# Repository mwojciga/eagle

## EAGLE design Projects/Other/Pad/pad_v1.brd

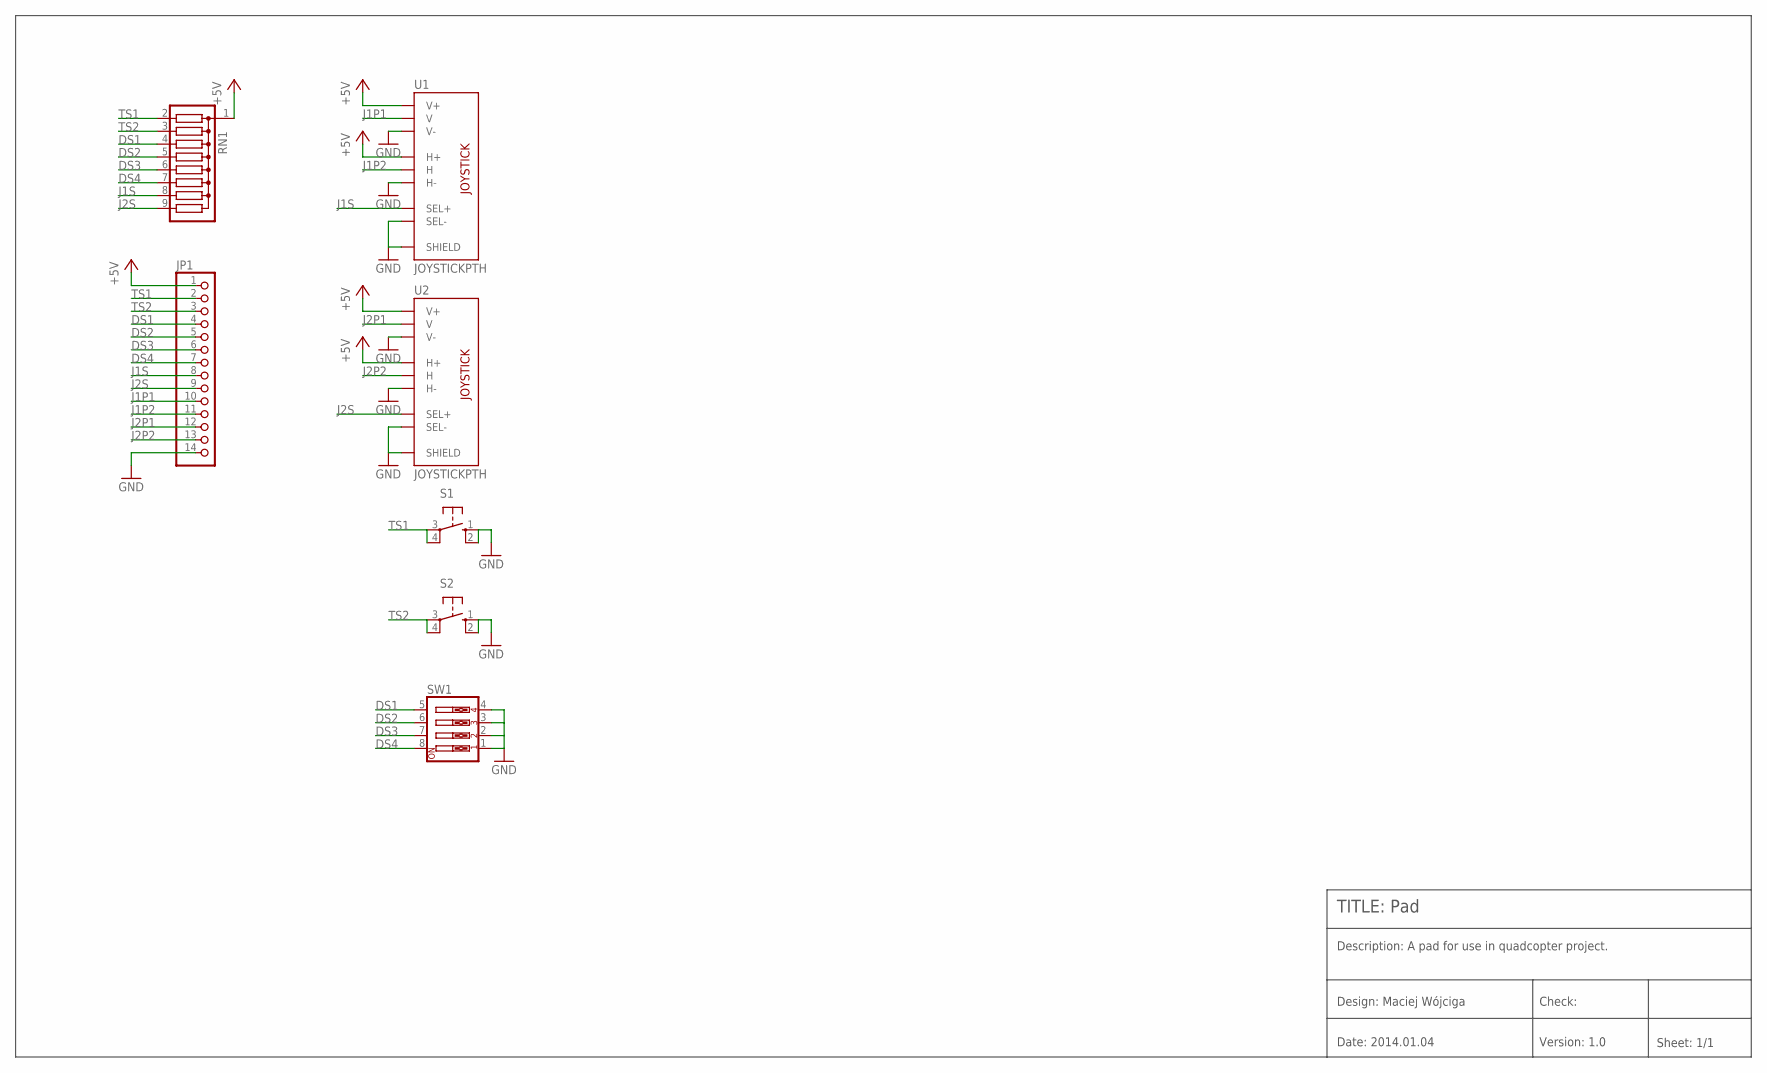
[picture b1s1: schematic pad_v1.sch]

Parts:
JP1: PINHD-1X14; 1X14
RN1: G08R; SIL9
S1, S2: 10-XX; B3F-10XX
SW1: SW_DIP-4; EDG-04
U1, U2: JOYSTICKPTH; JOYSTICK

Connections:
+5V: JP1.1, RN1.1, U1.H1 (H+), U1.V1 (V+), U2.H1 (H+), U2.V1 (V+)
DS1: JP1.4, RN1.4, SW1.5
DS2: JP1.5, RN1.5, SW1.6
DS3: JP1.6, RN1.6, SW1.7
DS4: JP1.7, RN1.7, SW1.8
GND: JP1.14, S1.1 (S), S1.2 (S1), S2.1 (S), S2.2 (S1), SW1.1, SW1.2, SW1.3, SW1.4, U1.B2A (SEL-), U1.B2B (SEL-), U1.H3 (H-), U1.MOUNT1 (SHIELD), U1.MOUNT2 (SHIELD), U1.MOUNT3 (SHIELD), U1.MOUNT4 (SHIELD), U1.V3 (V-), U2.B2A (SEL-), U2.B2B (SEL-), U2.H3 (H-), U2.MOUNT1 (SHIELD), U2.MOUNT2 (SHIELD), U2.MOUNT3 (SHIELD), U2.MOUNT4 (SHIELD), U2.V3 (V-)
J1P1: JP1.10, U1.V2 (V)
J1P2: JP1.11, U1.H2 (H)
J1S: JP1.8, RN1.8, U1.B1A (SEL+), U1.B1B (SEL+)
J2P1: JP1.12, U2.V2 (V)
J2P2: JP1.13, U2.H2 (H)
J2S: JP1.9, RN1.9, U2.B1A (SEL+), U2.B1B (SEL+)
TS1: JP1.2, RN1.2, S1.3, S1.4 (P1)
TS2: JP1.3, RN1.3, S2.3, S2.4 (P1)

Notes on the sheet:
TITLE: Pad
Design: Maciej Wójciga
Check:
Date: 2014.01.04
Version: 1.0
Sheet: 1/1
Description: A pad for use in quadcopter project.

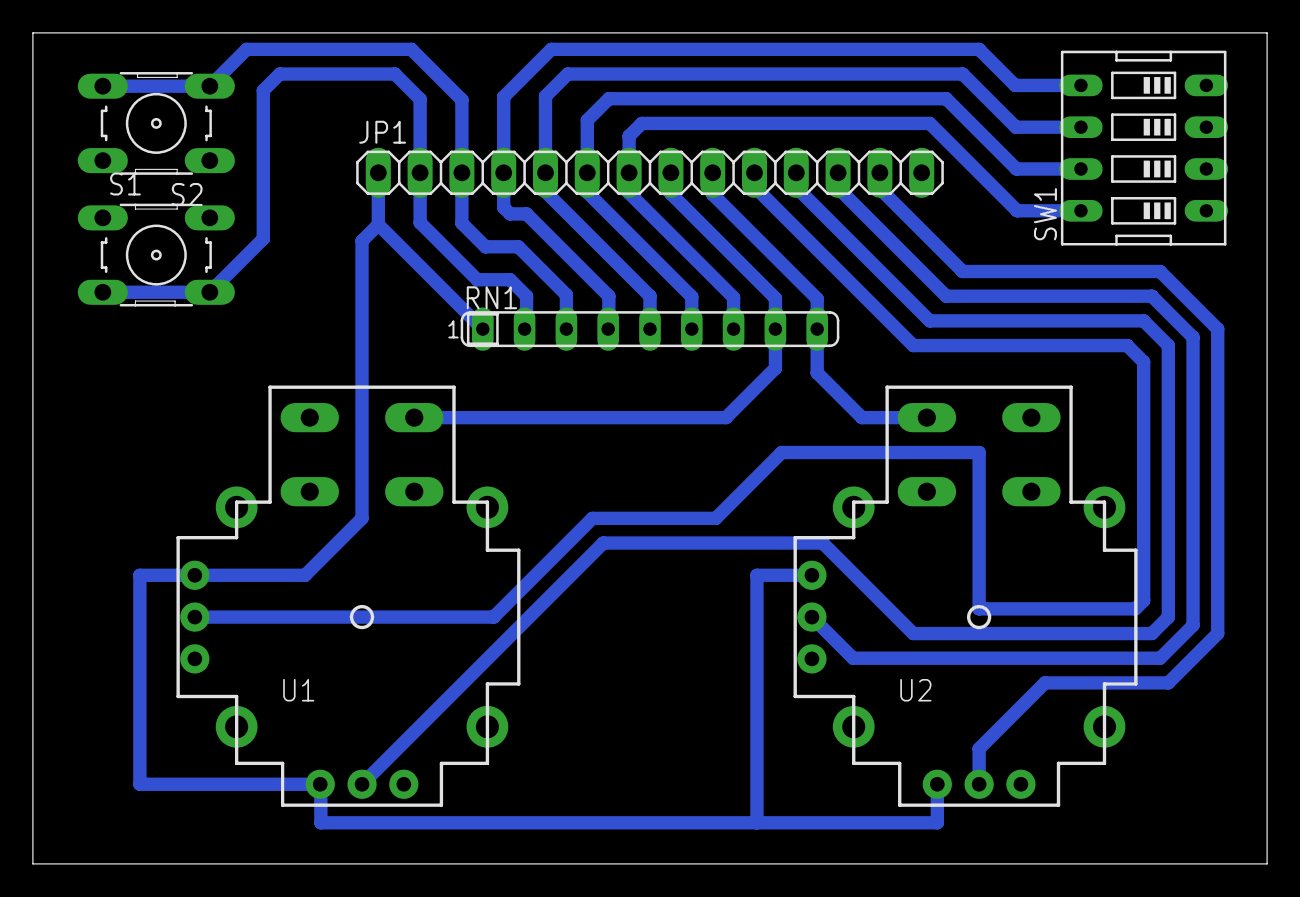
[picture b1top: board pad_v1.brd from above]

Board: 2 copper layers, 75.0 x 50.5 mm, 7 parts (0 on the bottom side), 14 nets.

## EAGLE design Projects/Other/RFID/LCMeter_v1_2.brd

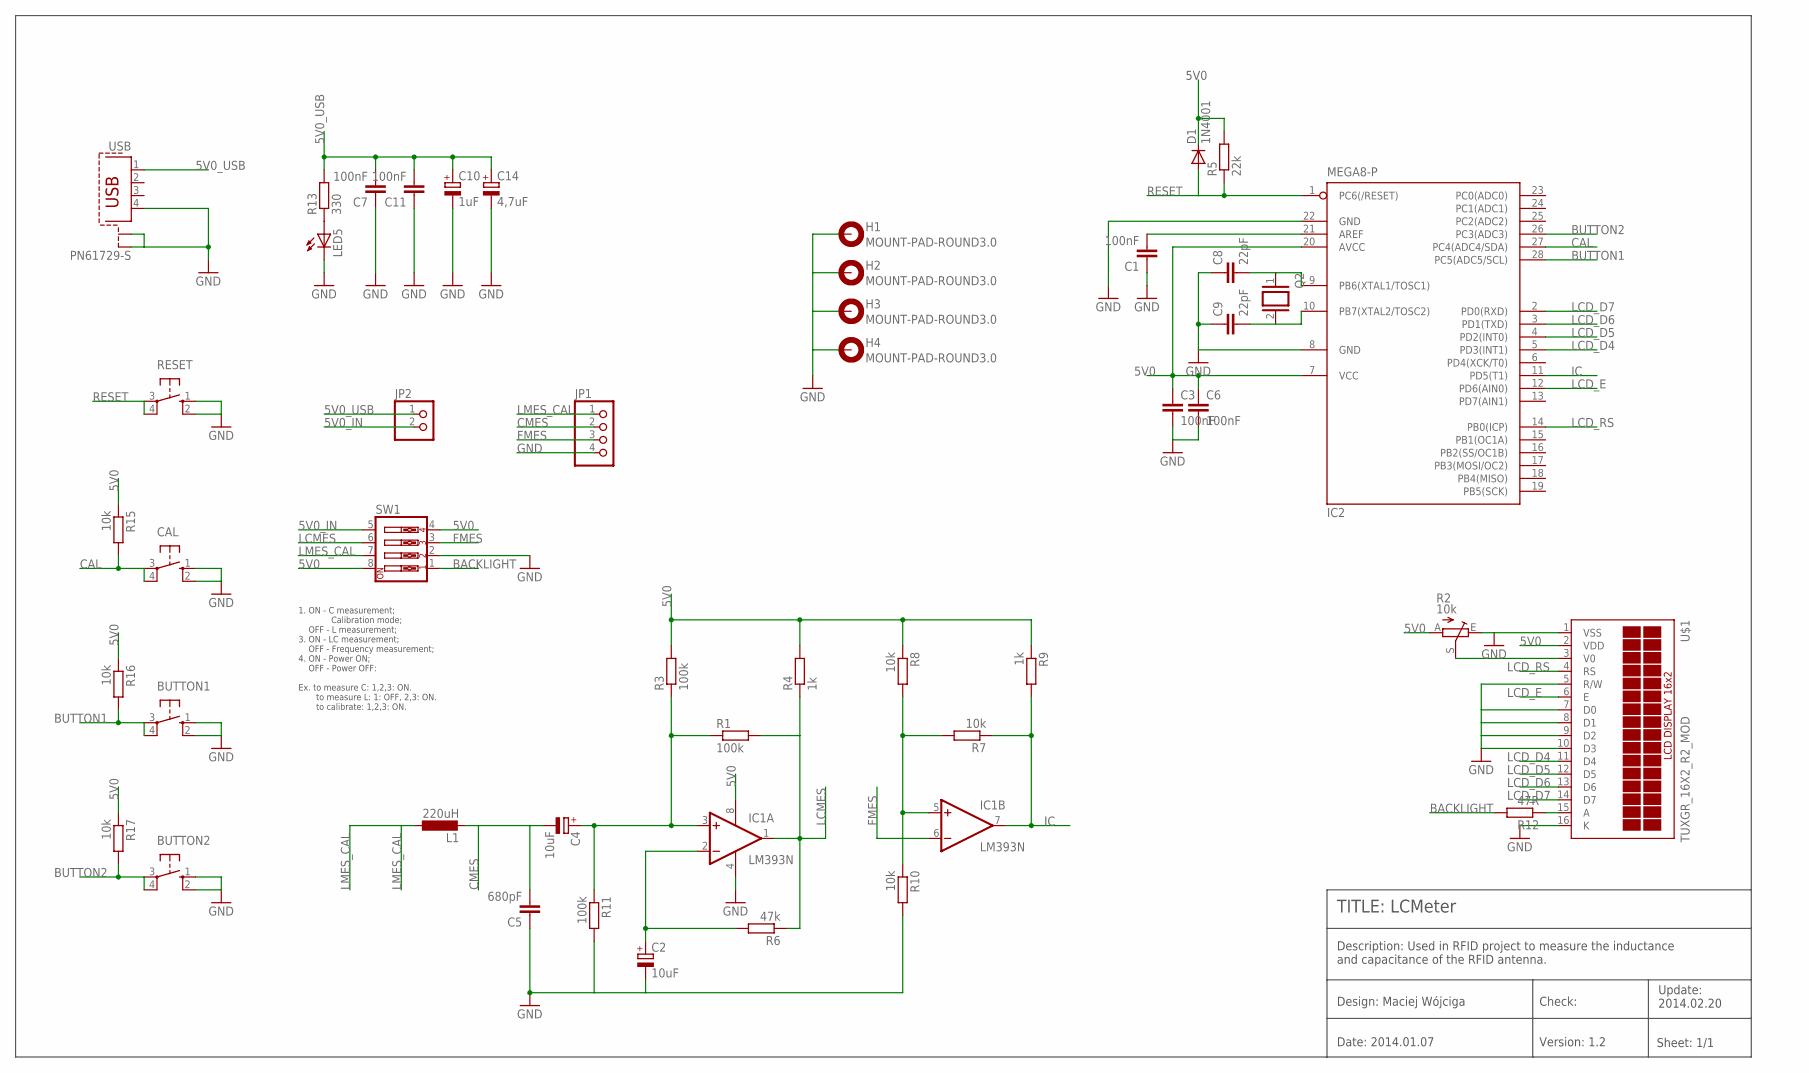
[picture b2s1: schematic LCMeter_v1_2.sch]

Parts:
BUTTON1, BUTTON2: 10-XX; B3F-10XX
C1, C3, C6, C7, C11: 100nF; C025-025X050
C2, C4: 10uF; E2,5-6E
C5: 680pF; C025-025X050
C8, C9: 22pF; C025-025X050
C10: 1uF; E2,5-5
C14: 4,7uF; E2,5-5
CAL: 10-XX; B3F-10XX
D1: 1N4001; DO41-10
H1, H2, H3, H4: MOUNT-PAD-ROUND3.0; 3,0-PAD
IC1: LM393N; DIL08
IC2: MEGA8-P; DIL28-3
JP1: PINHD-1X4; 1X04
JP2: PINHD-1X2/90; 1X02/90
L1: 220uH; 6000-XXXX-RC
LED5: LED3MM
Q2: XTAL/S; QS
R1, R3, R11: 100k; 0207/10
R2: 10k; RJ9W
R4, R9: 1k; 0207/10
R5: 22k; 0207/10
R6: 47k; 0207/10
R7, R8, R10, R15, R16, R17: 10k; 0207/10
R12: 47R; 0207/10
R13: 330; 0207/10
RESET: 10-XX; B3F-10XX
SW1: SW_DIP-4; EDG-04
U$1: TUXGR_16X2_R2_MOD
USB: PN61729-S

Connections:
5V0: C3.1, C6.1, D1.C, IC1.8 (V+), IC2.7 (VCC), IC2.20 (AVCC), R2.A, R3.2, R4.2, R5.2, R8.1, R9.1, R15.1, R16.1, R17.1, SW1.4, SW1.8, U$1.2 (VDD)
5V0_IN: JP2.2, SW1.5
5V0_USB: C7.2, C10.+, C11.2, C14.+, JP2.1, R13.2, USB.1
BACKLIGHT: R12.2, SW1.1
BUTTON1: BUTTON1.3, BUTTON1.4 (P1), IC2.28 (PC5(ADC5/SCL)), R16.2
BUTTON2: BUTTON2.3, BUTTON2.4 (P1), IC2.26 (PC3(ADC3)), R17.2
CAL: CAL.3, CAL.4 (P1), IC2.27 (PC4(ADC4/SDA)), R15.2
CMES: C4.-, C5.2, JP1.2, L1.2
FMES: IC1.6 (-IN), JP1.3, SW1.3
GND: BUTTON1.1 (S), BUTTON1.2 (S1), BUTTON2.1 (S), BUTTON2.2 (S1), C1.1, C2.-, C3.2, C5.1, C6.2, C7.1, C8.1, C9.1, C10.-, C11.1, C14.-, CAL.1 (S), CAL.2 (S1), H1.B3,0, H2.B3,0, H3.B3,0, H4.B3,0, IC1.4 (V-), IC2.8 (GND), IC2.22 (GND), JP1.4, LED5.K (C), R2.E, R10.2, R11.2, RESET.1 (S), RESET.2 (S1), SW1.2, U$1.1 (VSS), U$1.5 (R/W), U$1.7 (D0), U$1.8 (D1), U$1.9 (D2), U$1.10 (D3), U$1.16 (K), USB.4, USB.S1, USB.S2
IC: IC1.7 (OUT), IC2.11 (PD5(T1)), R7.1, R9.2
LCD_D4: IC2.5 (PD3(INT1)), U$1.11 (D4)
LCD_D5: IC2.4 (PD2(INT0)), U$1.12 (D5)
LCD_D6: IC2.3 (PD1(TXD)), U$1.13 (D6)
LCD_D7: IC2.2 (PD0(RXD)), U$1.14 (D7)
LCD_E: IC2.12 (PD6(AIN0)), U$1.6 (E)
LCD_RS: IC2.14 (PB0(ICP)), U$1.4 (RS)
LCMES: IC1.1 (OUT), R1.2, R4.1, R6.1, SW1.6
LMES_CAL: JP1.1, L1.1, SW1.7
unnamed: C1.2, IC2.21 (AREF)
unnamed: C2.+, IC1.2 (-IN), R6.2
unnamed: R2.S, U$1.3 (V0)
unnamed: C4.+, IC1.3 (+IN), R1.1, R3.1, R11.1
unnamed: LED5.A, R13.1
unnamed: IC1.5 (+IN), R7.2, R8.2, R10.1
unnamed: R12.1, U$1.15 (A)
unnamed: C8.2, IC2.9 (PB6(XTAL1/TOSC1)), Q2.1
unnamed: C9.2, IC2.10 (PB7(XTAL2/TOSC2)), Q2.2
RESET: D1.A, IC2.1 (PC6(/RESET)), R5.1, RESET.3, RESET.4 (P1)

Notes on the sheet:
TITLE: LCMeter
Design: Maciej Wójciga
Check:
Date: 2014.01.07
Version: 1.2
Sheet: 1/1
Description: Used in RFID project to measure the inductance and capacitance of the RFID antenna.
1. ON - C measurement; Calibration mode; OFF - L measurement; 3. ON - LC measurement; OFF - Frequency measurement; 4. ON - Power ON; OFF - Power OFF: Ex. to measure C: 1,2,3: ON. to measure L: 1: OFF, 2,3: ON. to calibrate: 1,2,3: ON.
Update: 2014.02.20

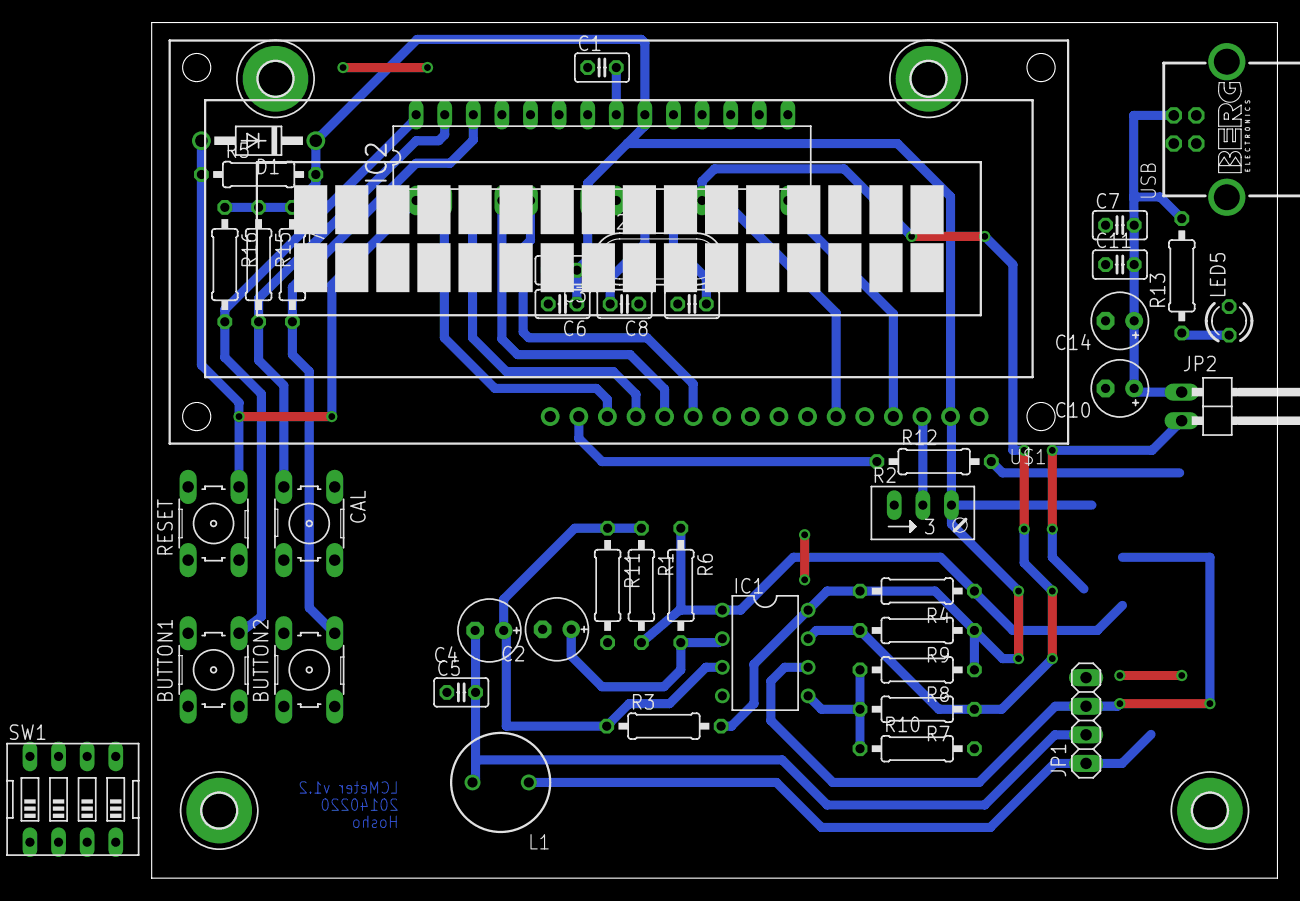
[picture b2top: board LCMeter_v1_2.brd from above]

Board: 2 copper layers, 100.0 x 76.0 mm, 47 parts (0 on the bottom side), 29 nets.

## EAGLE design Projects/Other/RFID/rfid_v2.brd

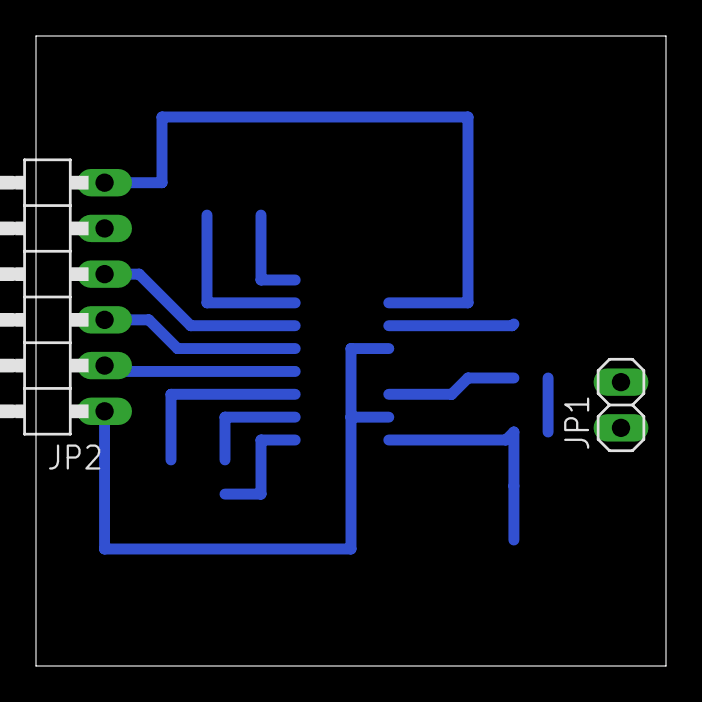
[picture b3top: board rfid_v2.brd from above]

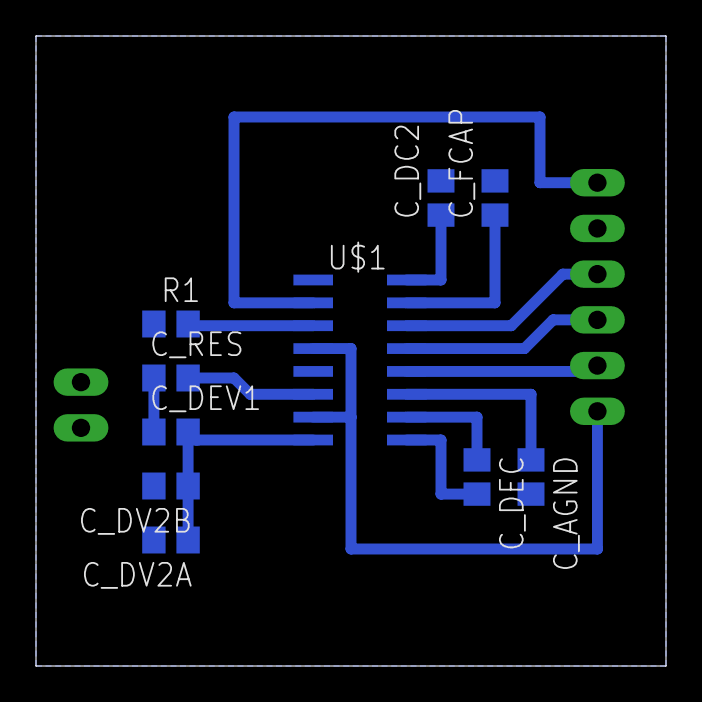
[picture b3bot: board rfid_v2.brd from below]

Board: 2 copper layers, 35.0 x 35.0 mm, 12 parts (10 on the bottom side), 16 nets.

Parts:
C_AGND: 100n; C0805
C_DC2: 10n; C0805
C_DEC: 100n; C0805
C_DEV1: 4p7; C0805
C_DV2A: 1n0; C0805
C_DV2B: 470p; C0805
C_FCAP: 10n; C0805
C_RES: 3n3; C0805
JP1: 1X02
JP2: 1X06/90
R1: 33R; R0805
U$1: EM4095_MOD; SO16

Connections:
+5V: JP2.1, U$1.4, U$1.7
DMOD_OUT: JP2.3, U$1.13
GND: C_AGND.2, C_DC2.2, C_DV2A.2, C_DV2B.2, C_FCAP.2, JP2.5, U$1.1, U$1.5
MOD: JP2.2, U$1.12
unnamed: C_DEV1.2, C_DV2A.1, C_DV2B.1, U$1.8
unnamed: C_RES.2, U$1.6
unnamed: JP1.2, R1.1
unnamed: R1.2, U$1.3
unnamed: C_DEV1.1, C_RES.1, JP1.1
unnamed: C_DEC.1, U$1.10
unnamed: C_DEC.2, U$1.9
unnamed: C_AGND.1, U$1.11
unnamed: C_DC2.1, U$1.16
unnamed: C_FCAP.1, U$1.15
RDY/CLK: JP2.6, U$1.2
SHD: JP2.4, U$1.14

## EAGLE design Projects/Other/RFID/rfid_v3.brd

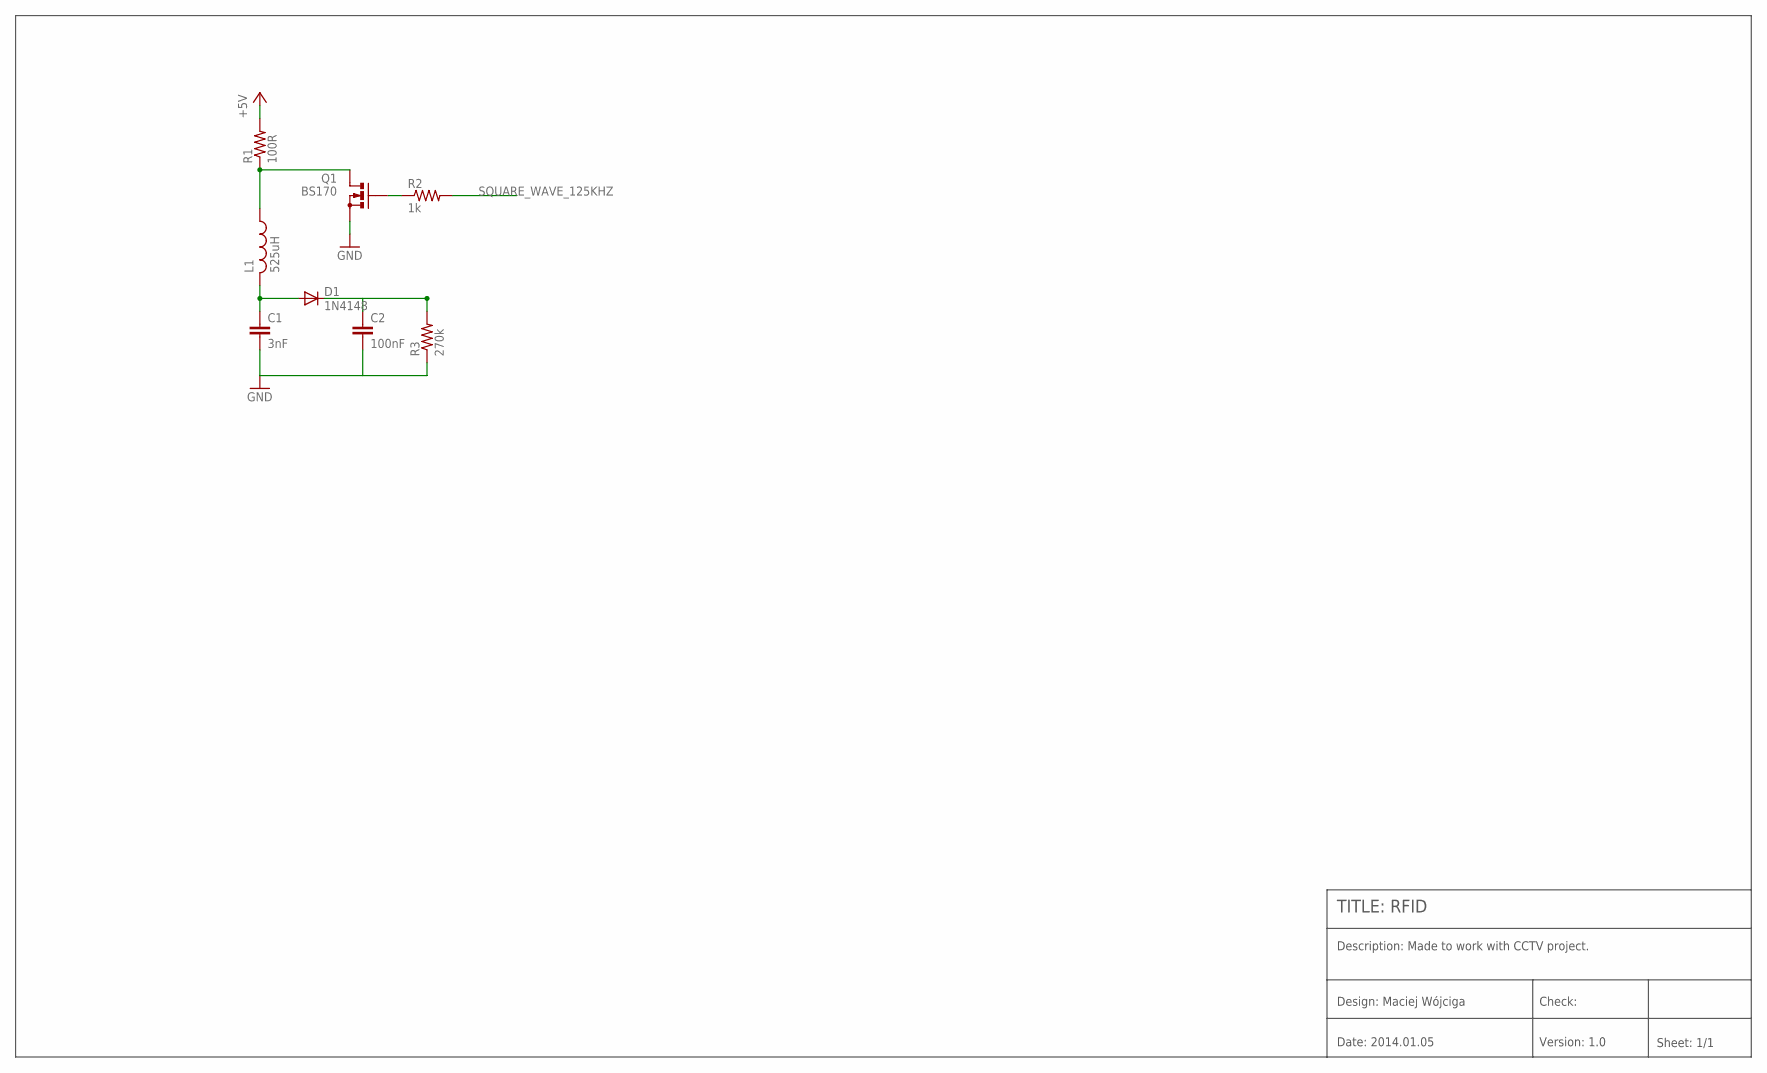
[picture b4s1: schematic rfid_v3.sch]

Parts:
C1: 3nF; C025-050X050
C2: 100nF; C025-050X050
D1: 1N4148; DO35-7
L1: 525uH; 0204/5
Q1: BS170; SOT54E
R1: 100R; 0309/10
R2: 1k; 0309/10
R3: 270k; 0309/10

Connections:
+5V: R1.2
GND: C1.2, C2.2, Q1.S, R3.1
unnamed: Q1.G, R2.1
unnamed: L1.1, Q1.D, R1.1
unnamed: C1.1, D1.A, L1.2
unnamed: C2.1, D1.C, R3.2
SQUARE_WAVE_125KHZ: R2.2

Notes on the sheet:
TITLE: RFID
Design: Maciej Wójciga
Check:
Date: 2014.01.05
Version: 1.0
Sheet: 1/1
Description: Made to work with CCTV project.

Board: 2 copper layers, 8 parts (0 on the bottom side), 5 nets, no tracks yet.
